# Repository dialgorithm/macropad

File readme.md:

# macropad

xiao esp32s3 based 10 key custom wireless macropad with a display to show the current layer and controls.

There are 10 keys, 1 layer switch button, 1 rotary encoder, and a slide switch for turning on and off.

## Schematics + PCB

Designed using KiCad.

| Schematic                          | PCB Layout             | 3D PCB                     |
| ---------------------------------- | ---------------------- | -------------------------- |
|  |  |  |

## CAD

I am using cnc'd acrylic transparent sheets to keep a minimal and clean look.

| Top View                   | Side View                    | Bottom View                      |
| -------------------------- | ---------------------------- | -------------------------------- |
|  |  |  |

## BOM

you can find the detailed bill of materials [here](bom.csv)

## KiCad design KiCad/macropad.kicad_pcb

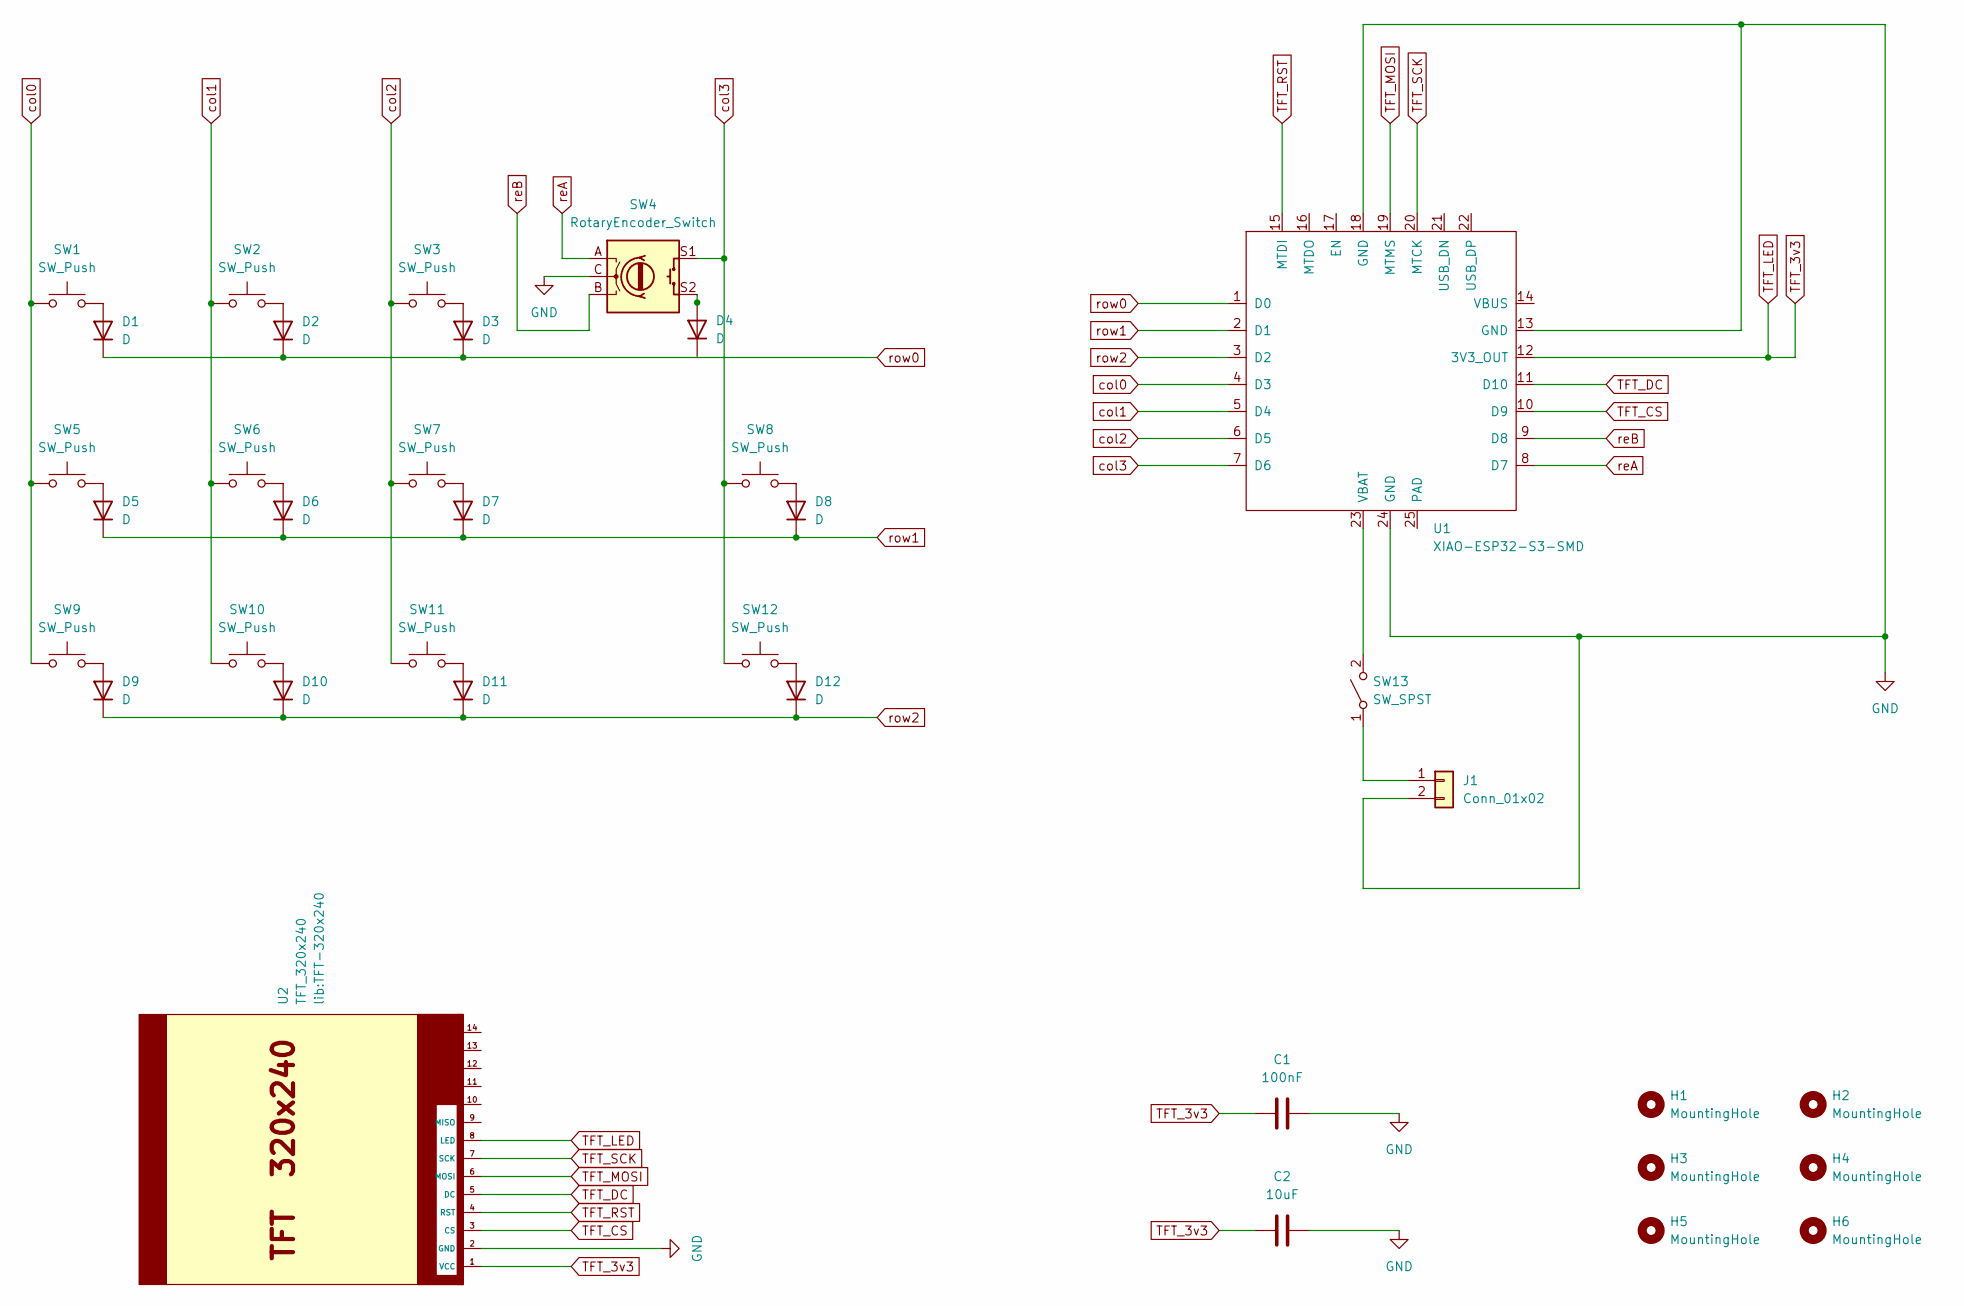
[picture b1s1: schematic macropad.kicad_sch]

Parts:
C1: 100nF; C_0603_1608Metric
C2: 10uF; C_0805_2012Metric
D1, D2, D3, D4, D5, D6, D7, D8, D9, D10, D11, D12: D; D_SOD-123
H1, H2, H3, H4, H5, H6: MountingHole; MountingHole_2.2mm_M2_ISO7380
J1: Conn_01x02; JST_PH_S2B-PH-K_1x02_P2.00mm_Horizontal
SW1, SW2, SW3, SW5, SW6, SW7, SW8, SW9, SW10, SW11: SW_Push; SW_Cherry_MX_1.00u_PCB
SW4: RotaryEncoder_Switch; RotaryEncoder_Alps_EC11E-Switch_Vertical_H20mm
SW12: SW_Push; SW_PUSH_6mm
SW13: SW_SPST; SW_Slide_SPDT_Straight_CK_OS102011MS2Q
U1: XIAO-ESP32-S3-SMD
U2: TFT_320x240; TFT-320x240

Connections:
GND: C1.2, C2.2, J1.2, SW4.C, U1.13 (GND), U1.18 (GND), U1.24 (GND), U2.2 (GND)
unnamed: D1.2 (A), SW1.2
unnamed: D2.2 (A), SW2.2
unnamed: D3.2 (A), SW3.2
unnamed: D4.2 (A_2), SW4.S2
unnamed: D5.2 (A), SW5.2
unnamed: D6.2 (A), SW6.2
unnamed: D7.2 (A), SW7.2
unnamed: D8.2 (A), SW8.2
unnamed: D9.2 (A), SW9.2
unnamed: D10.2 (A), SW10.2
unnamed: D11.2 (A), SW11.2
unnamed: D12.2 (A), SW12.2
unnamed: J1.1, SW13.1 (A)
unnamed: SW13.2 (B), U1.23 (VBAT)
TFT_3v3: C1.1, C2.1, U1.12 (3V3_OUT), U2.1 (VCC), U2.8 (LED)
TFT_CS: U1.10 (D9), U2.3 (CS)
TFT_DC: U1.11 (D10), U2.5 (DC)
TFT_MOSI: U1.19 (MTMS), U2.6 (MOSI)
TFT_RST: U1.15 (MTDI), U2.4 (RST)
TFT_SCK: U1.20 (MTCK), U2.7 (SCK)
col0: SW1.1, SW5.1, SW9.1, U1.4 (D3)
col1: SW2.1, SW6.1, SW10.1, U1.5 (D4)
col2: SW3.1, SW7.1, SW11.1, U1.6 (D5)
col3: SW4.S1, SW8.1, SW12.1, U1.7 (D6)
reA: SW4.A, U1.8 (D7)
reB: SW4.B, U1.9 (D8)
row0: D1.1 (K), D2.1 (K), D3.1 (K), U1.1 (D0)
row1: D5.1 (K), D6.1 (K), D7.1 (K), D8.1 (K), U1.2 (D1)
row2: D9.1 (K), D10.1 (K), D11.1 (K), D12.1 (K), U1.3 (D2)

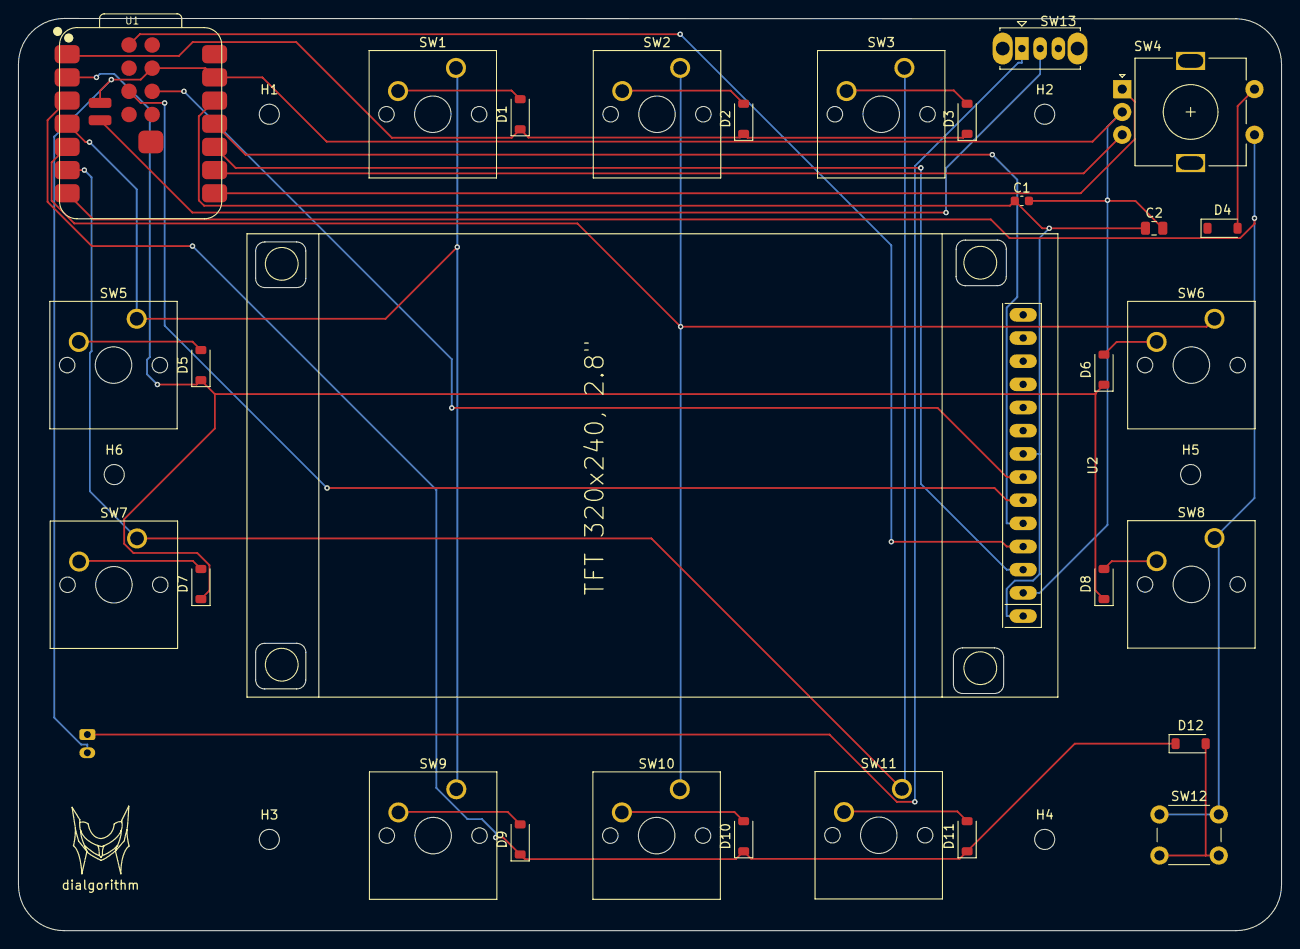
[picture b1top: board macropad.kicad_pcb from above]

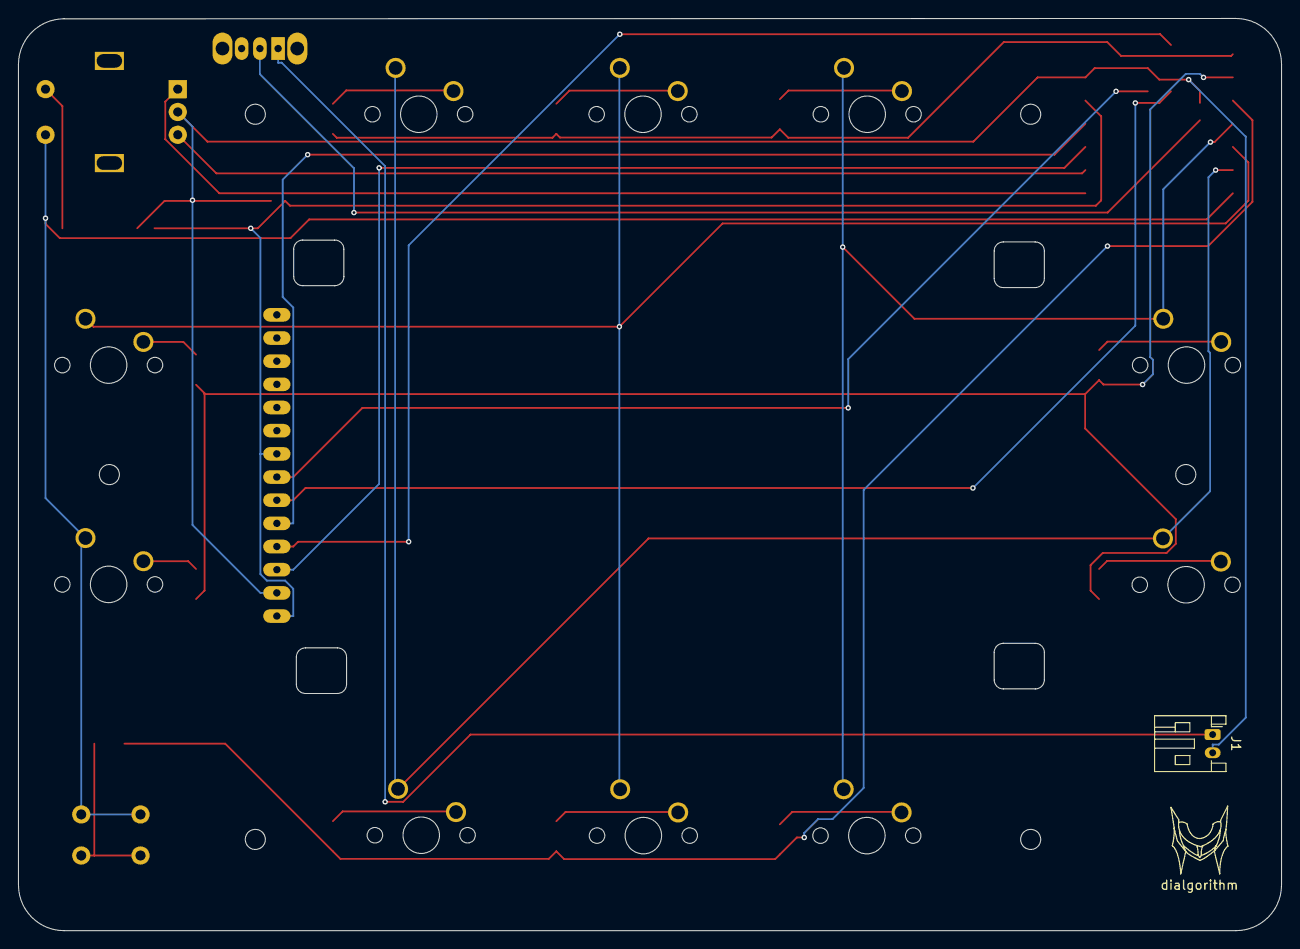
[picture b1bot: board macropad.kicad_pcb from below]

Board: 2 copper layers, 138.5 x 100.0 mm, 38 parts (2 on the bottom side), 30 nets.

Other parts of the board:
dialgorithm: dialgorithm
dialgorithm#2: dialgorithm
